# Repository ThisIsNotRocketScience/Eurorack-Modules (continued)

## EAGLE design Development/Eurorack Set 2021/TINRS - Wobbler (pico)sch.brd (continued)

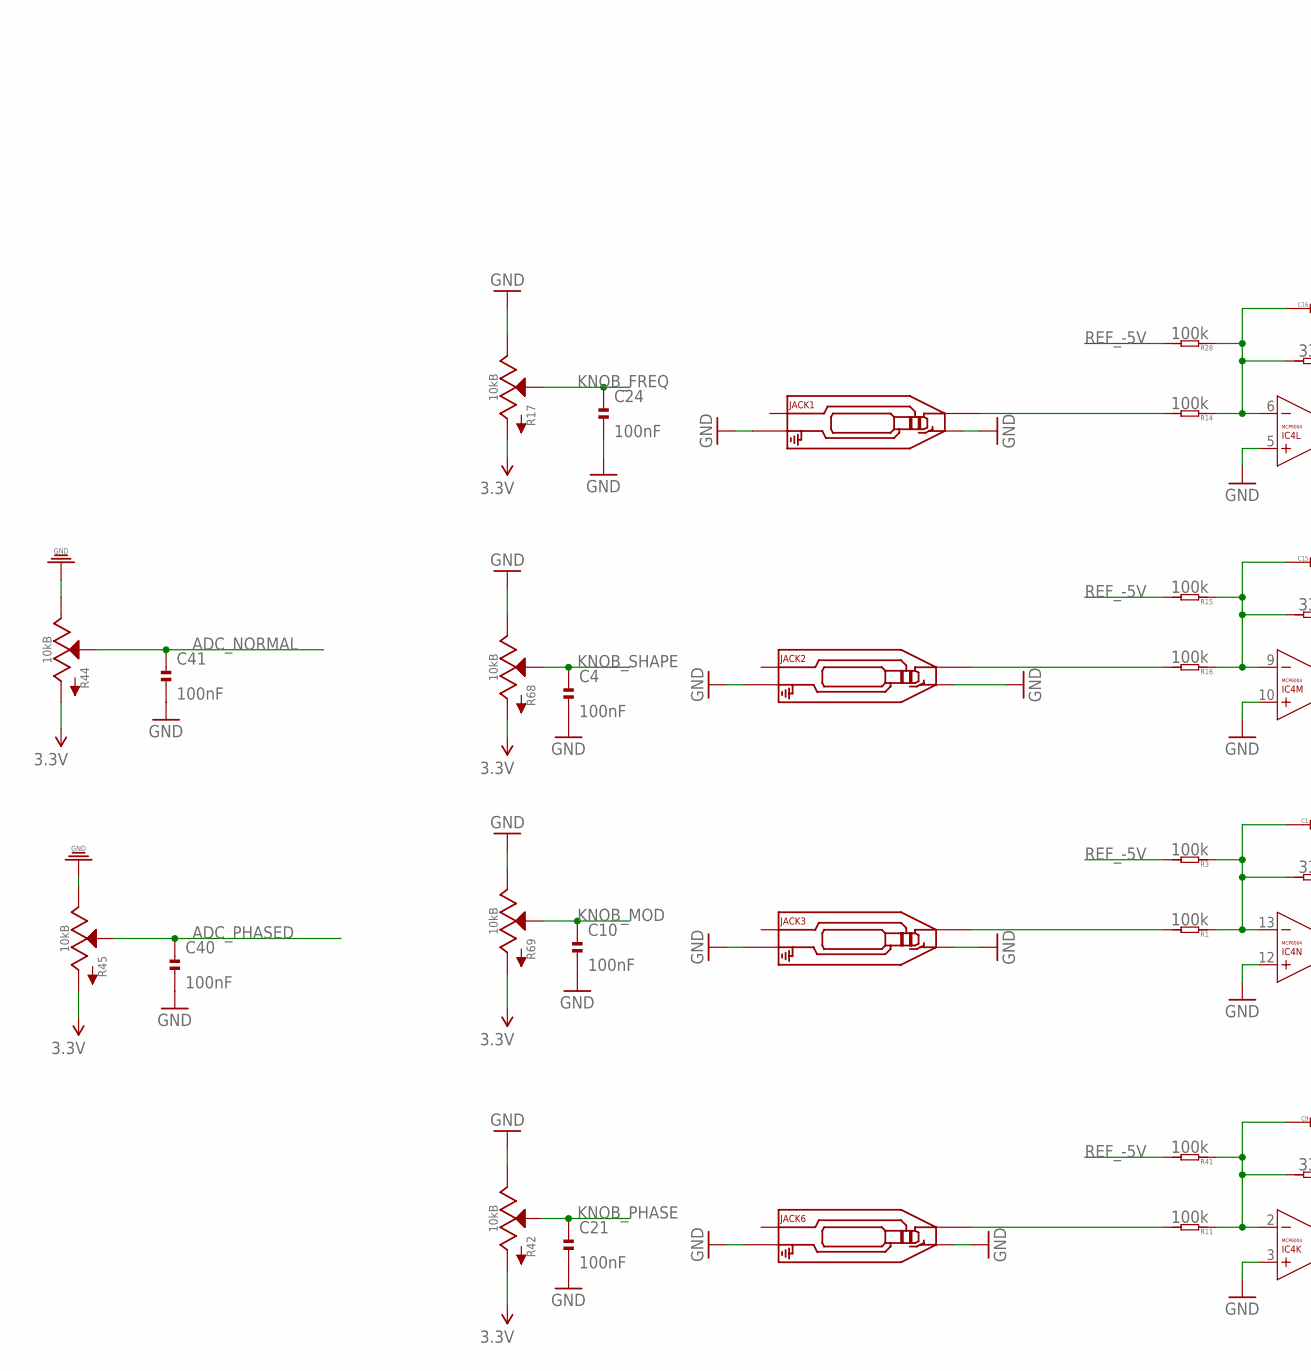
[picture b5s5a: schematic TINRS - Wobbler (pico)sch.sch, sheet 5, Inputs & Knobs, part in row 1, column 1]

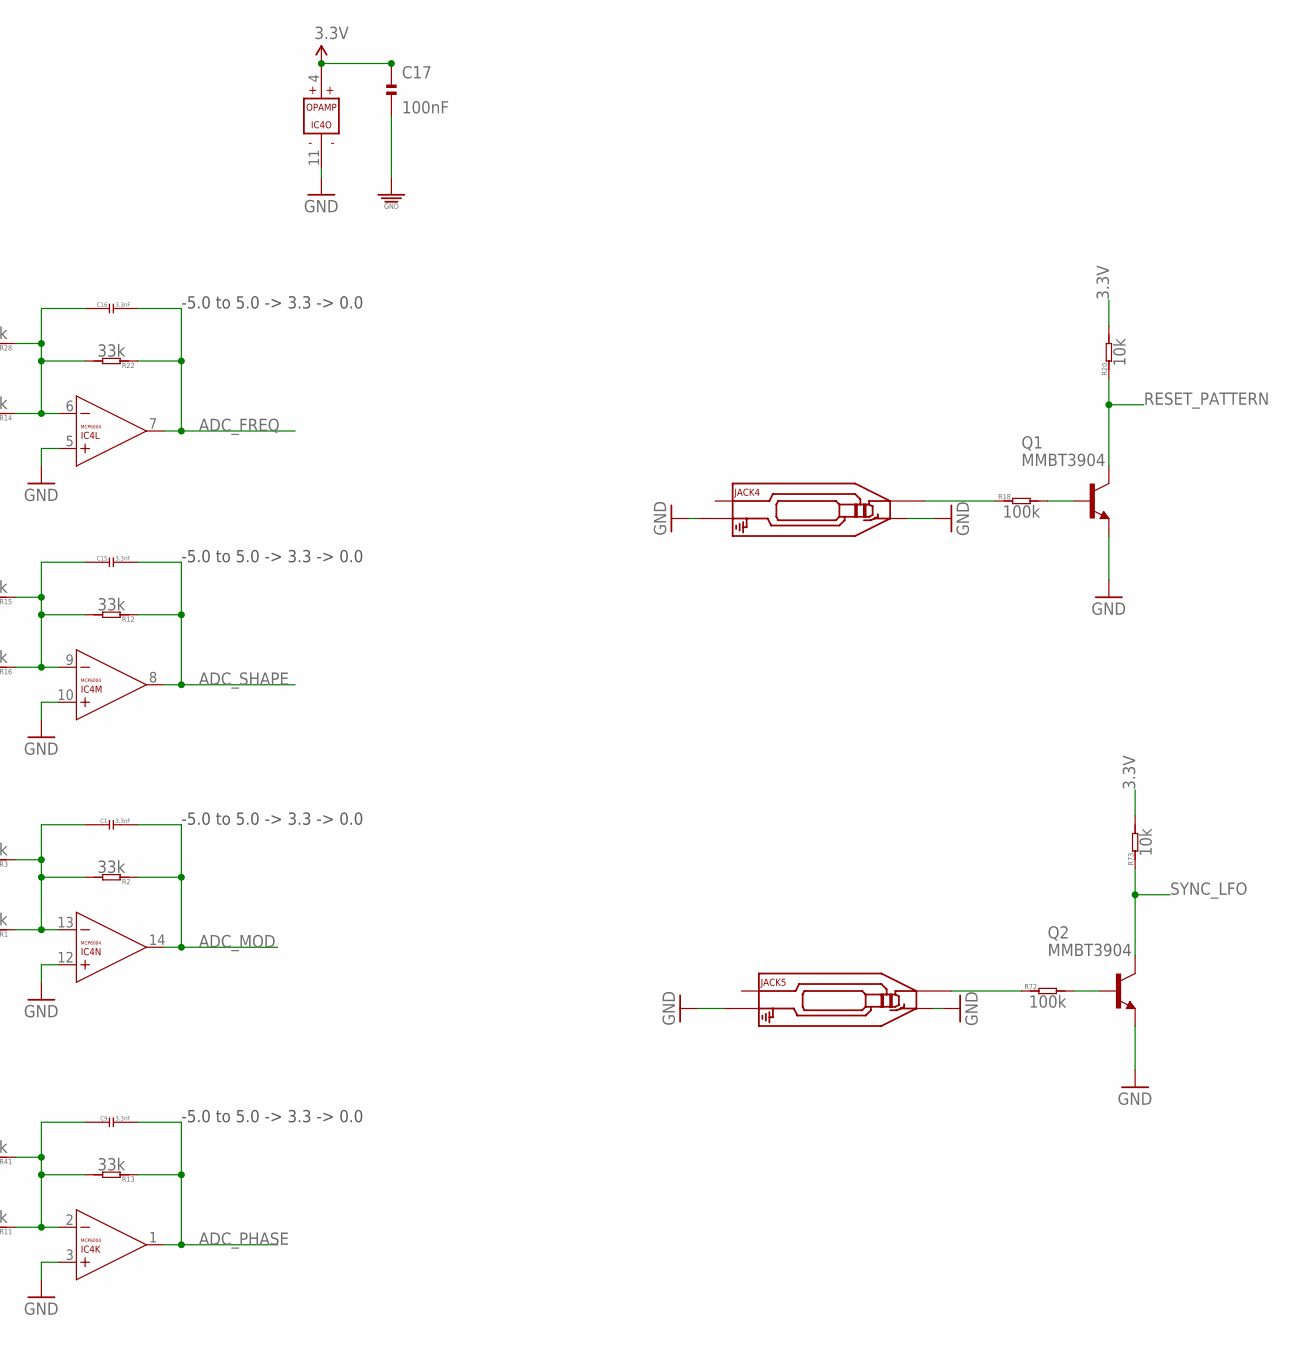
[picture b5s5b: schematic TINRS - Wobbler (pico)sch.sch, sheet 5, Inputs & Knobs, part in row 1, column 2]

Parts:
C1, C9, C15, C16: 3.3nF; C0603
C4, C10, C17, C21, C24, C40, C41: 100nF; C0402; MPN MC0603F104Z160CT
IC4: MCP6004; SO14; MPN MCP6004-I/SL.
JACK1, JACK2, JACK3, JACK4, JACK5, JACK6: AUDIO-JACK_SMALLSYMBOL; 3.5MM-JACK-SWITCH-13MM-NOHOLES-TESTPAD
Q1, Q2: MMBT3904; SOT23-BEC; MPN PMBT3904,215
R1, R3, R11, R14, R15, R16, R18, R28, R41, R72: 100k; R0603
R2, R12, R13, R22: 33k; R0603
R17, R42, R44, R45, R68, R69: 10kB; ALPS_POT_SQUAREHOLES
R20, R73: 10k; R0603

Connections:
3.3V: C17.1, IC4.4 (V+), R17.P$3 (A), R20.2, R42.P$3 (A), R44.P$3 (A), R45.P$3 (A), R68.P$3 (A), R69.P$3 (A), R73.2; also elsewhere on the board
ADC_FREQ: C16.2, IC4.7 (OUT), R22.1; also elsewhere on the board
ADC_MOD: C1.2, IC4.14 (OUT), R2.1; also elsewhere on the board
ADC_NORMAL: C41.1, R44.P$2 (S); also elsewhere on the board
ADC_PHASE: C9.2, IC4.1 (OUT), R13.1; also elsewhere on the board
ADC_PHASED: C40.1, R45.P$2 (S); also elsewhere on the board
ADC_SHAPE: C15.2, IC4.8 (OUT), R12.1; also elsewhere on the board
GND: C4.2, C10.2, C17.2, C21.2, C24.2, C40.2, C41.2, IC4.3 (+IN), IC4.5 (+IN), IC4.10 (+IN), IC4.11 (V-), IC4.12 (+IN), JACK1.RING_B@1 (RING), JACK1.RING_T@3 (RING), JACK1.SWITCH_B@1 (SWITCH), JACK1.SWITCH_T@3 (SWITCH), JACK2.RING_B@1 (RING), JACK2.RING_T@3 (RING), JACK2.SWITCH_B@1 (SWITCH), JACK2.SWITCH_T@3 (SWITCH), JACK3.RING_B@1 (RING), JACK3.RING_T@3 (RING), JACK3.SWITCH_B@1 (SWITCH), JACK3.SWITCH_T@3 (SWITCH), JACK4.RING_B@1 (RING), JACK4.RING_T@3 (RING), JACK4.SWITCH_B@1 (SWITCH), JACK4.SWITCH_T@3 (SWITCH), JACK5.RING_B@1 (RING), JACK5.RING_T@3 (RING), JACK5.SWITCH_B@1 (SWITCH), JACK5.SWITCH_T@3 (SWITCH), JACK6.RING_B@1 (RING), JACK6.RING_T@3 (RING), JACK6.SWITCH_B@1 (SWITCH), JACK6.SWITCH_T@3 (SWITCH), Q1.E, Q2.E, R17.P$1 (E), R42.P$1 (E), R44.P$1 (E), R45.P$1 (E), R68.P$1 (E), R69.P$1 (E); also elsewhere on the board
KNOB_FREQ: C24.1, R17.P$2 (S); also elsewhere on the board
KNOB_MOD: C10.1, R69.P$2 (S); also elsewhere on the board
KNOB_PHASE: C21.1, R42.P$2 (S); also elsewhere on the board
KNOB_SHAPE: C4.1, R68.P$2 (S); also elsewhere on the board
unnamed: JACK2.TIP_B@1 (TIP), JACK2.TIP_T@3 (TIP), R16.2
unnamed: C15.1, IC4.9 (-IN), R12.2, R15.1, R16.1
unnamed: JACK3.TIP_B@1 (TIP), JACK3.TIP_T@3 (TIP), R1.2
unnamed: C1.1, IC4.13 (-IN), R1.1, R2.2, R3.1
unnamed: JACK6.TIP_B@1 (TIP), JACK6.TIP_T@3 (TIP), R11.2
unnamed: C9.1, IC4.2 (-IN), R11.1, R13.2, R41.1
unnamed: Q1.B, R18.2
unnamed: JACK4.TIP_B@1 (TIP), JACK4.TIP_T@3 (TIP), R18.1
unnamed: JACK1.TIP_B@1 (TIP), JACK1.TIP_T@3 (TIP), R14.2
unnamed: C16.1, IC4.6 (-IN), R14.1, R22.2, R28.1
unnamed: Q2.B, R72.2
unnamed: JACK5.TIP_B@1 (TIP), JACK5.TIP_T@3 (TIP), R72.1
REF_-5V: R3.2, R15.2, R28.2, R41.2; also elsewhere on the board
RESET_PATTERN: Q1.C, R20.1; also elsewhere on the board
SYNC_LFO: Q2.C, R73.1; also elsewhere on the board

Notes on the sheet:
-5.0 to 5.0 -> 3.3 -> 0.0

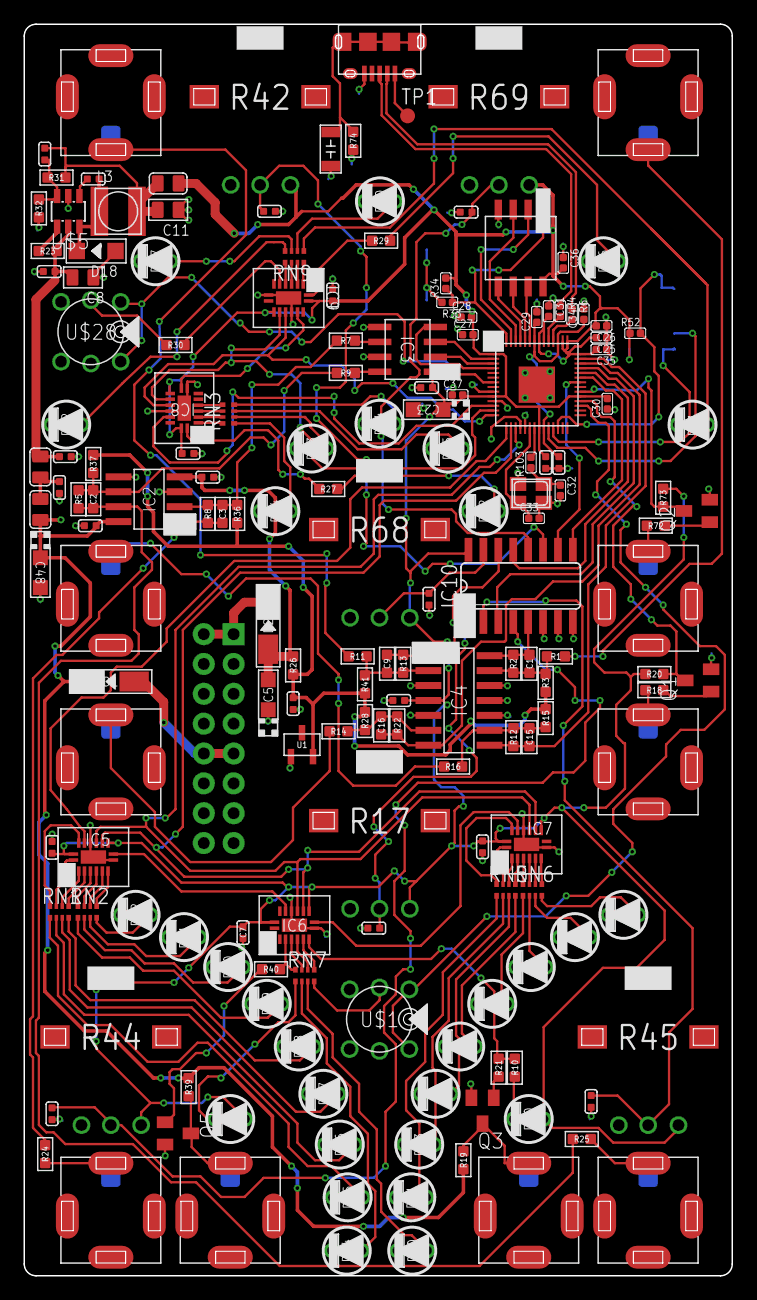
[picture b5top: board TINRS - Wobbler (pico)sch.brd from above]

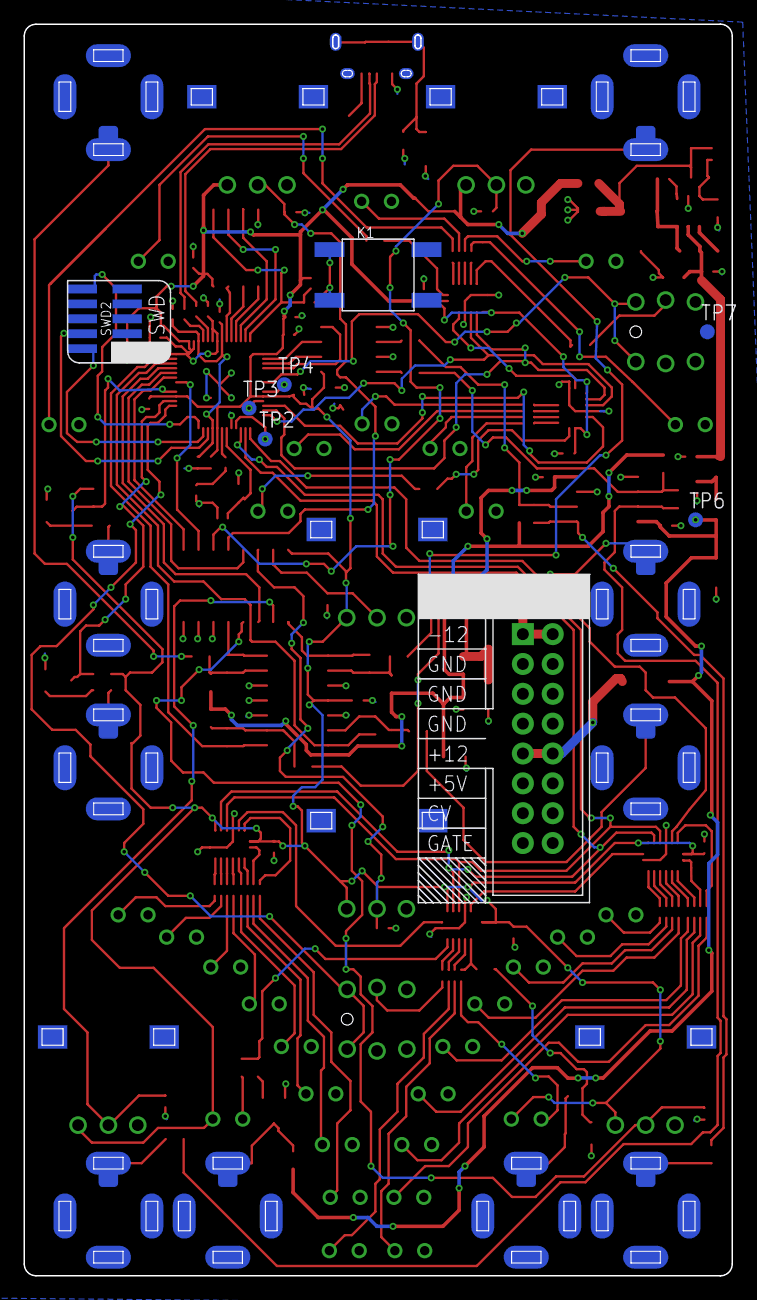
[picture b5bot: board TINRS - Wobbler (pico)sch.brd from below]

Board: 2 copper layers, 60.2 x 106.5 mm, 182 parts (8 on the bottom side), 155 nets.

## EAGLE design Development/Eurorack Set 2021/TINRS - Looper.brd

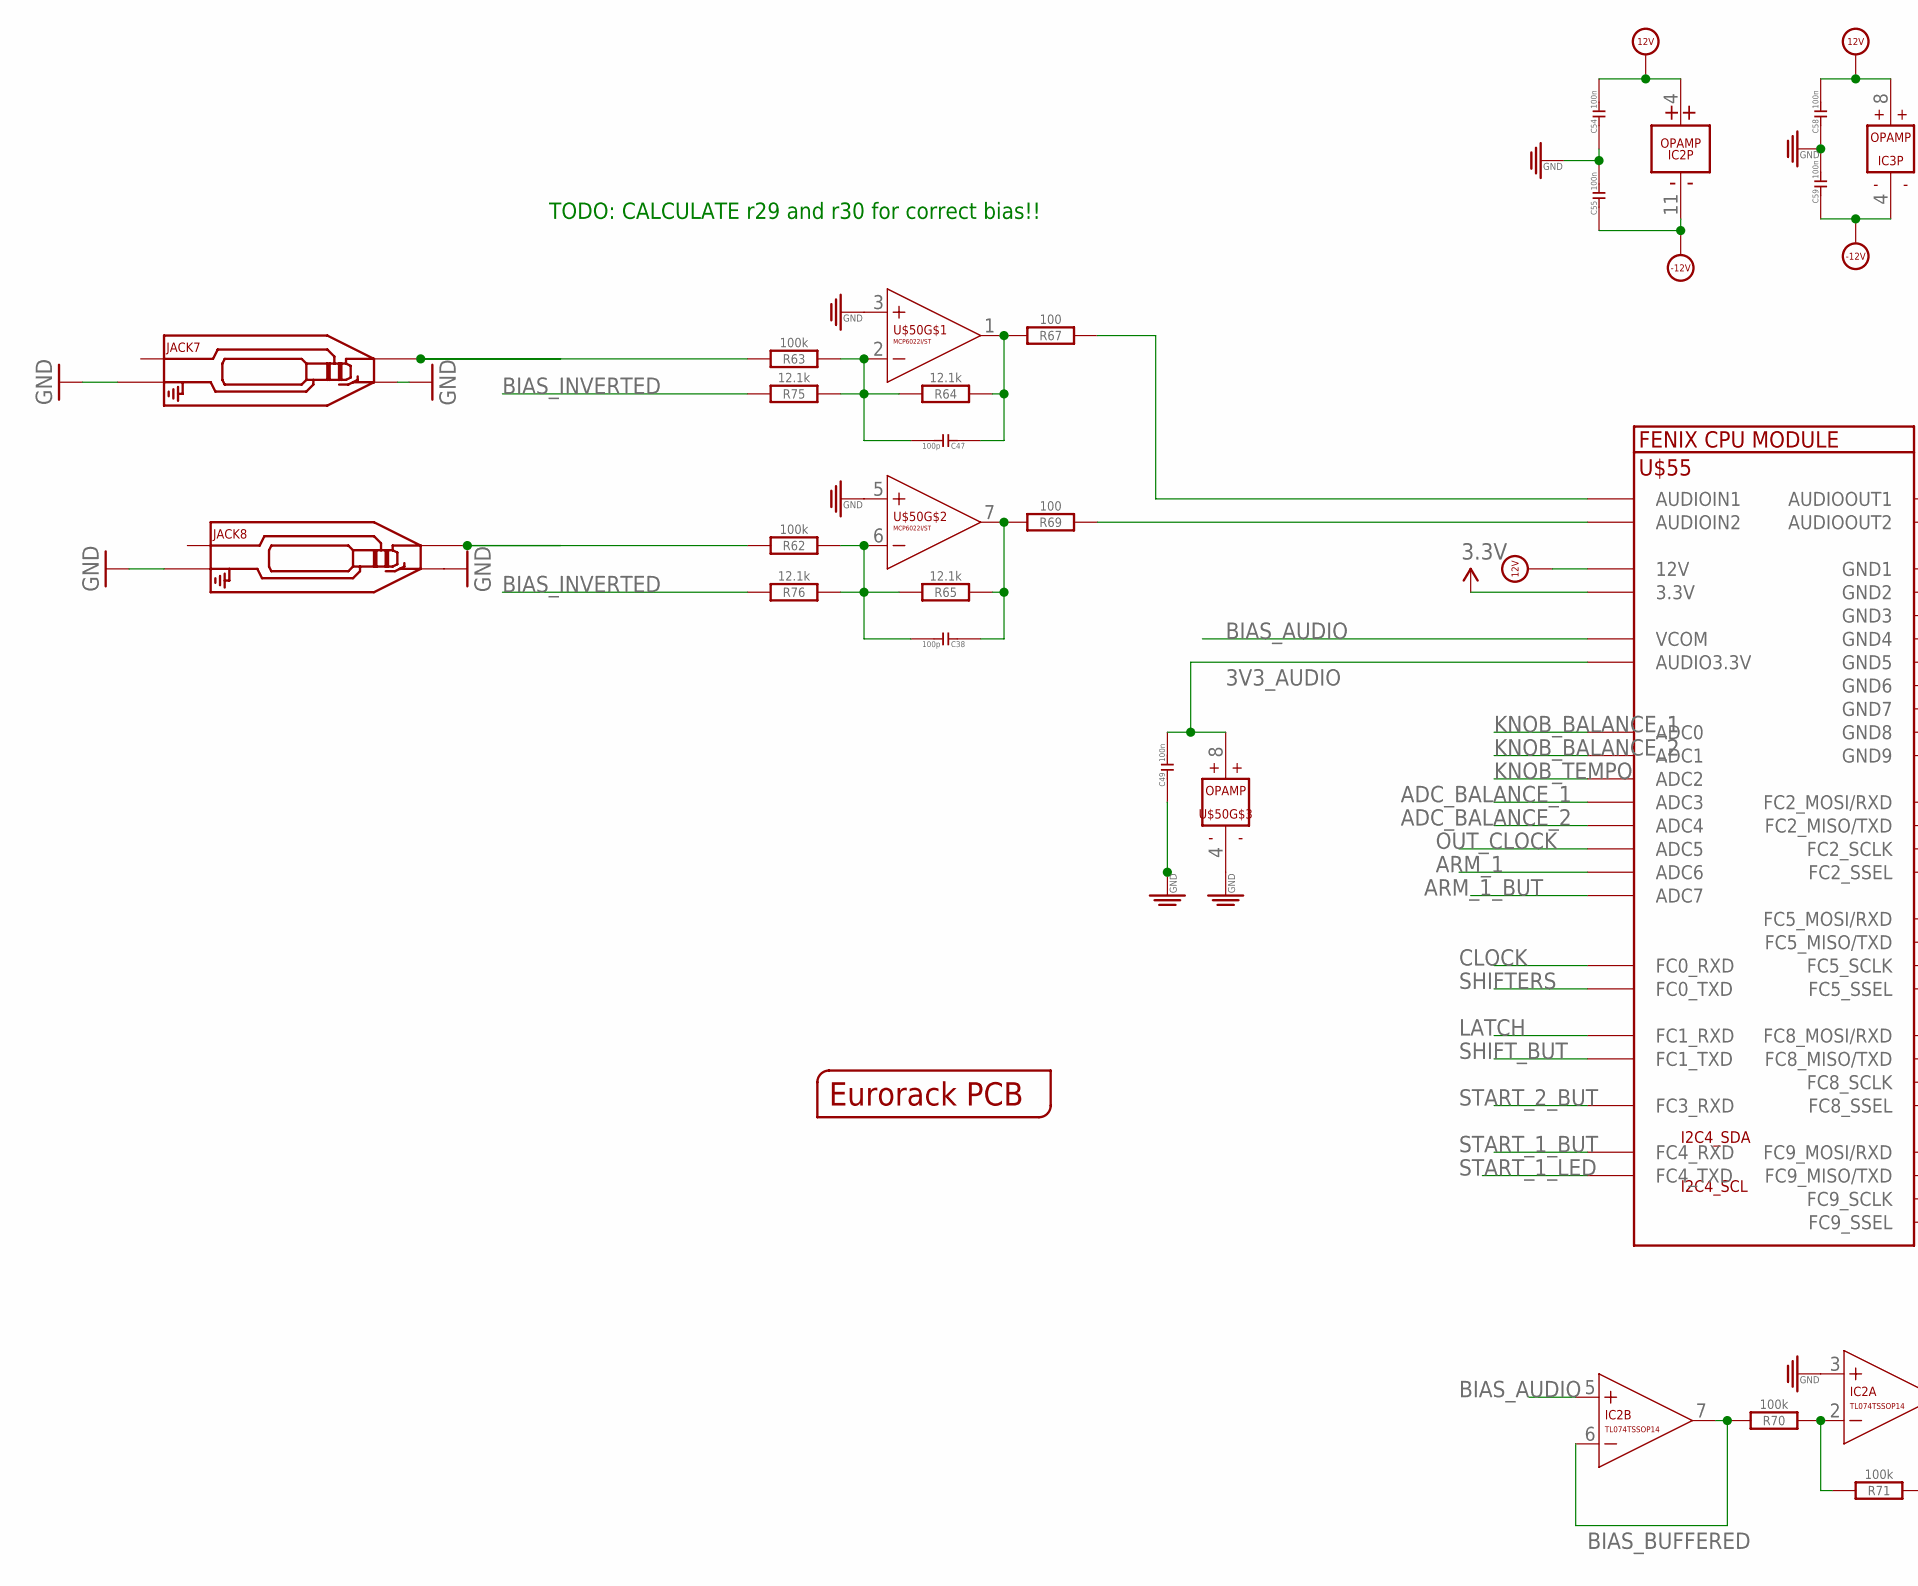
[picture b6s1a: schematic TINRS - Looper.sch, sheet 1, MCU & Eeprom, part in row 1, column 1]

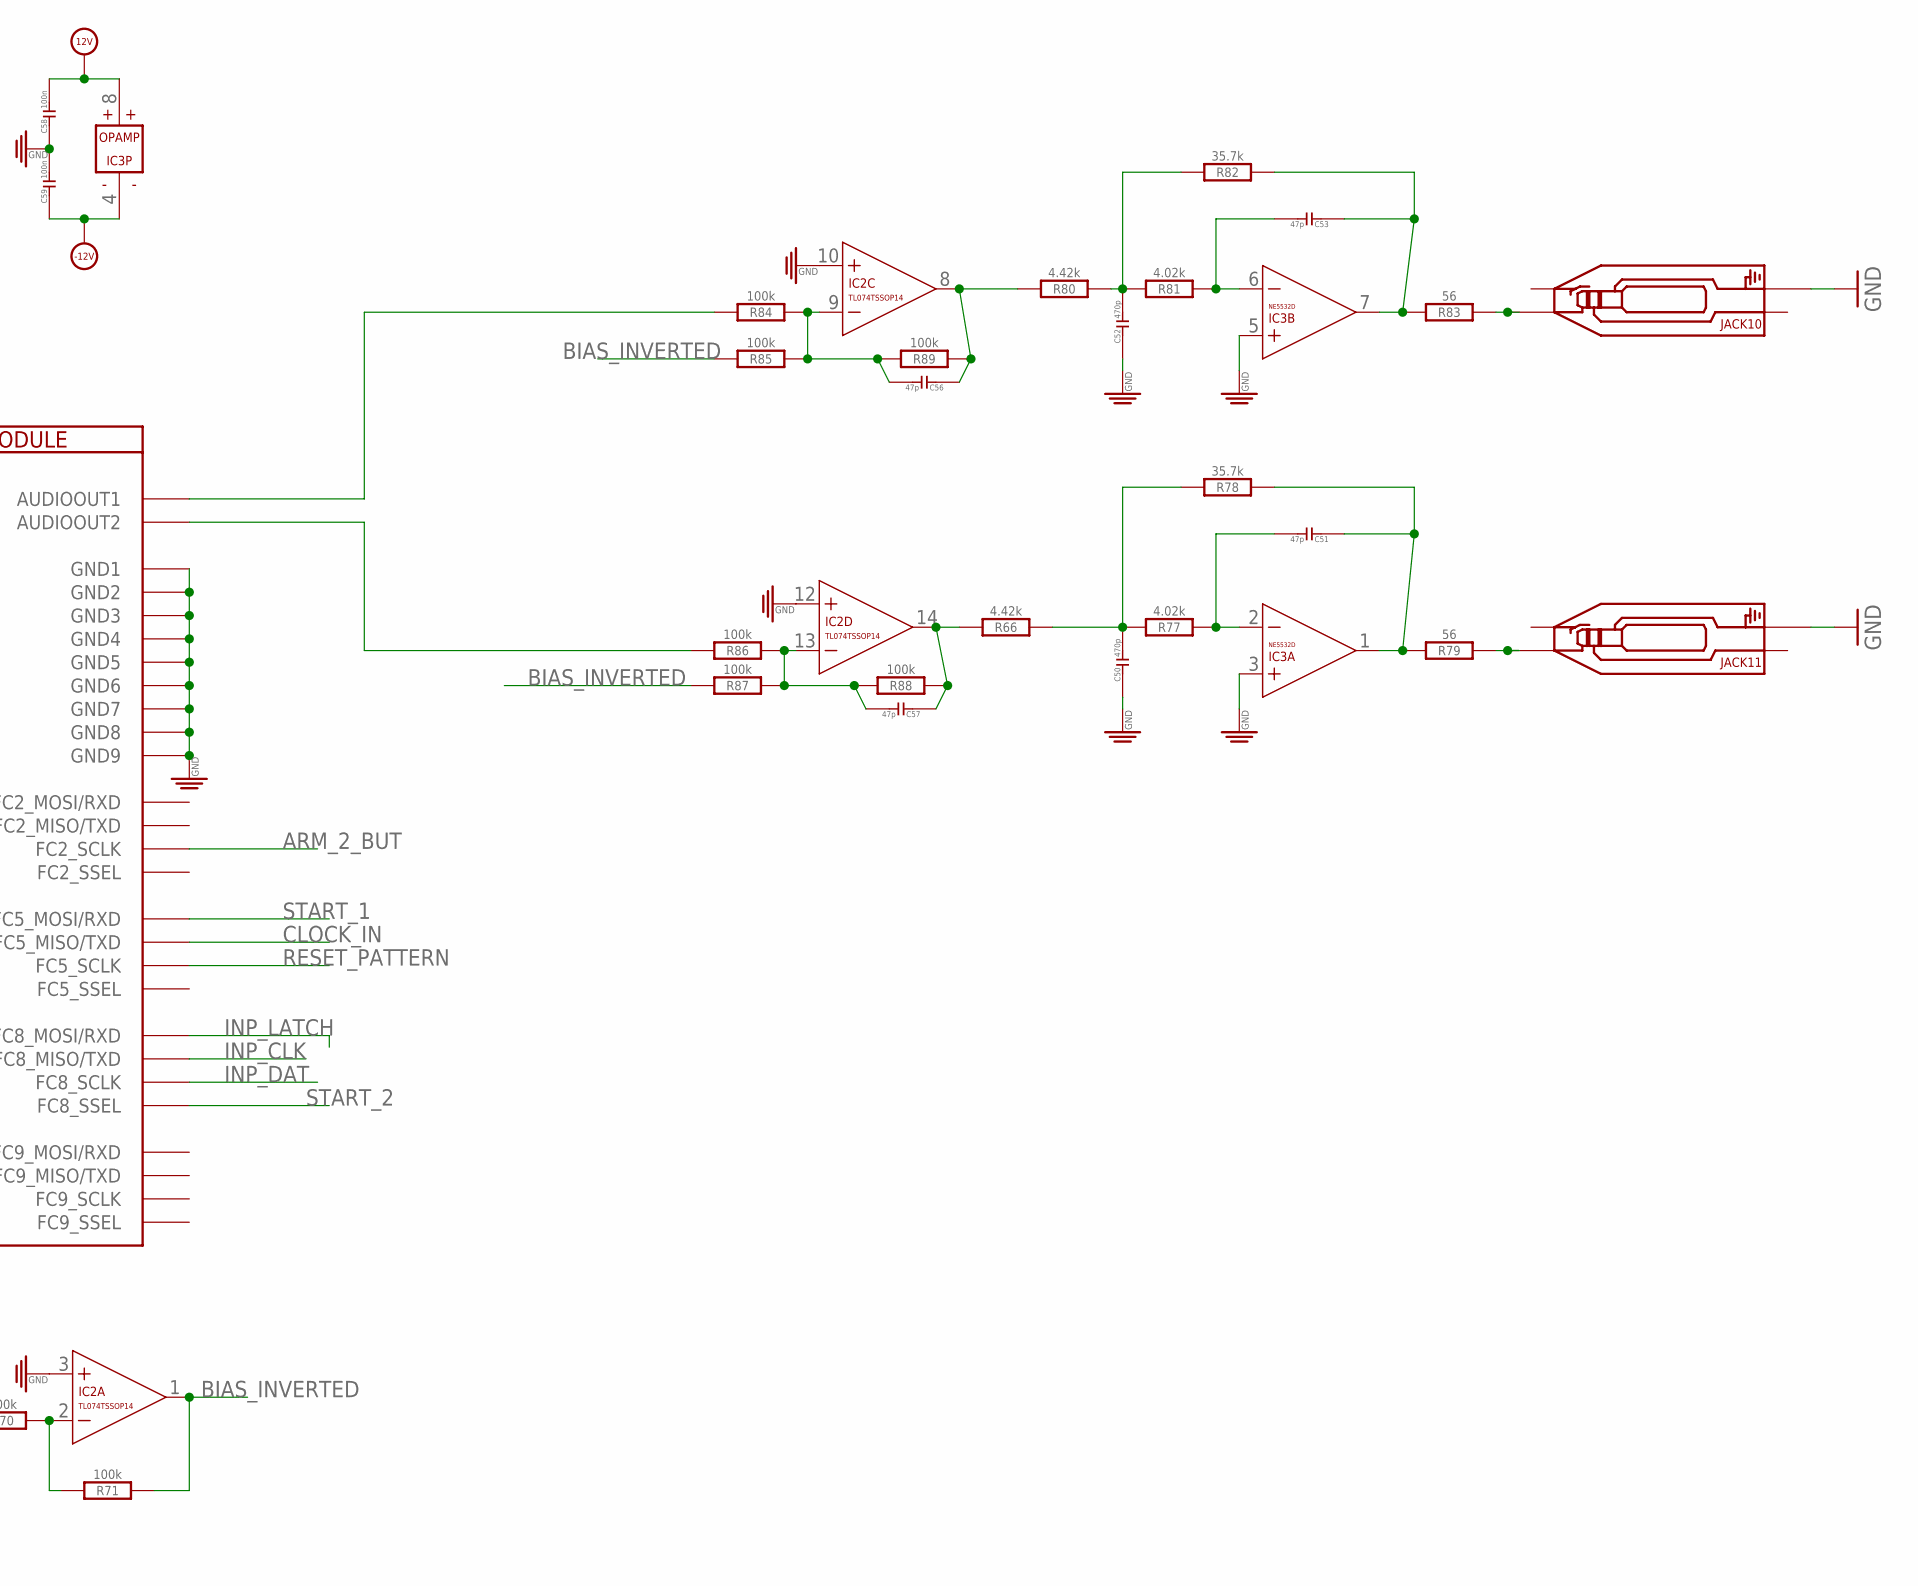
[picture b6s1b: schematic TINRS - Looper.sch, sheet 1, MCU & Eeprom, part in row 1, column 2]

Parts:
C38, C47: 100p; C0603
C49, C54, C55, C58, C59: 100n; C0603
C50, C52: 470p; C0603
C51, C53, C56, C57: 47p; C0603
IC2: TL074TSSOP14; TSSOP14
IC3: NE5532D; SO08
JACK7, JACK8, JACK10, JACK11: AUDIO-JACK_SMALLSYMBOL; 3.5MM-JACK-SWITCH-13MM-NOHOLES-TESTPAD
OUTLINE: EURORACK_PCB12HP; EURORACK12HPPCB
R62, R63, R70, R71, R84, R85, R86, R87, R88, R89: 100k; R0402
R64, R65, R75, R76: 12.1k; R0402
R66, R80: 4.42k; R0402
R67, R69: 100; R0402
R77, R81: 4.02k; R0402
R78, R82: 35.7k; R0402
R79, R83: 56; R0402
U$50: MCP6022I/ST; TSSOP8
U$55: MCUPLUGIN2; MCUPLUGIN

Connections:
3.3V: U$55.P$7 (3.3V); also elsewhere on the board
3V3_AUDIO: C49.2, U$50.8 (V+), U$55.P$48 (AUDIO3.3V)
12V: C54.2, C58.2, IC2.4 (V+), IC3.8 (V+), U$55.P$45 (12V); also elsewhere on the board
-12V: C55.1, C59.1, IC2.11 (V-), IC3.4 (V-); also elsewhere on the board
ADC_BALANCE_1: U$55.P$28 (ADC3); also elsewhere on the board
ADC_BALANCE_2: U$55.P$29 (ADC4); also elsewhere on the board
ARM_1: U$55.P$31 (ADC6); also elsewhere on the board
ARM_1_BUT: U$55.P$32 (ADC7); also elsewhere on the board
ARM_2_BUT: U$55.P$11 (FC2_SCLK); also elsewhere on the board
BIAS_AUDIO: IC2.5 (+IN), U$55.P$47 (VCOM)
BIAS_BUFFERED: IC2.6 (-IN), IC2.7 (OUT), R70.1
BIAS_INVERTED: IC2.1 (OUT), R71.2, R75.1, R76.1, R85.1, R87.1
CLOCK: U$55.P$36 (FC0_RXD); also elsewhere on the board
CLOCK_IN: U$55.P$21 (FC5_MISO/TXD); also elsewhere on the board
GND: C49.1, C50.1, C52.1, C54.1, C55.2, C58.1, C59.2, IC2.3 (+IN), IC2.10 (+IN), IC2.12 (+IN), IC3.3 (+IN), IC3.5 (+IN), JACK7.RING_B@1 (RING), JACK7.RING_T@3 (RING), JACK7.SWITCH_B@1 (SWITCH), JACK7.SWITCH_T@3 (SWITCH), JACK8.RING_B@1 (RING), JACK8.RING_T@3 (RING), JACK8.SWITCH_B@1 (SWITCH), JACK8.SWITCH_T@3 (SWITCH), JACK10.RING_B@1 (RING), JACK10.RING_T@3 (RING), JACK11.RING_B@1 (RING), JACK11.RING_T@3 (RING), U$50.3 (+IN), U$50.4 (V-), U$50.5 (+IN), U$55.P$1 (GND1), U$55.P$6 (GND2), U$55.P$8 (GND3), U$55.P$23 (GND4), U$55.P$24 (GND5), U$55.P$33 (GND6), U$55.P$39 (GND7), U$55.P$40 (GND8), U$55.P$46 (GND9); also elsewhere on the board
INP_CLK: U$55.P$13 (FC8_MISO/TXD); also elsewhere on the board
INP_DAT: U$55.P$15 (FC8_SCLK); also elsewhere on the board
INP_LATCH: U$55.P$14 (FC8_MOSI/RXD); also elsewhere on the board
KNOB_BALANCE_1: U$55.P$25 (ADC0); also elsewhere on the board
KNOB_BALANCE_2: U$55.P$26 (ADC1); also elsewhere on the board
KNOB_TEMPO: U$55.P$27 (ADC2); also elsewhere on the board
LATCH: U$55.P$38 (FC1_RXD); also elsewhere on the board
unnamed: C38.2, R62.2, R65.1, R76.2, U$50.6 (-IN)
unnamed: C47.2, R63.2, R64.1, R75.2, U$50.2 (-IN)
unnamed: C38.1, R65.2, R69.1, U$50.7 (OUT)
unnamed: C47.1, R64.2, R67.1, U$50.1 (OUT)
unnamed: IC2.2 (-IN), R70.2, R71.1
unnamed: C51.2, IC3.2 (-IN), R77.2
unnamed: C50.2, R66.2, R77.1, R78.1
unnamed: C51.1, IC3.1 (OUT), R78.2, R79.1
unnamed: JACK11.TIP_B@1 (TIP), JACK11.TIP_T@3 (TIP), R79.2
unnamed: C53.2, IC3.6 (-IN), R81.2
unnamed: C52.2, R80.2, R81.1, R82.1
unnamed: C53.1, IC3.7 (OUT), R82.2, R83.1
unnamed: JACK10.TIP_B@1 (TIP), JACK10.TIP_T@3 (TIP), R83.2
unnamed: C56.2, IC2.9 (-IN), R84.2, R85.2, R89.1
unnamed: C57.2, IC2.13 (-IN), R86.2, R87.2, R88.1
unnamed: C56.1, IC2.8 (OUT), R80.1, R89.2
unnamed: R86.1, U$55.P$44 (AUDIOOUT2)
unnamed: R84.1, U$55.P$42 (AUDIOOUT1)
unnamed: C57.1, IC2.14 (OUT), R66.1, R88.2
unnamed: JACK7.TIP_B@1 (TIP), JACK7.TIP_T@3 (TIP), R63.1
unnamed: JACK8.TIP_B@1 (TIP), JACK8.TIP_T@3 (TIP), R62.1
OUT_CLOCK: U$55.P$30 (ADC5); also elsewhere on the board
RESET_PATTERN: U$55.P$20 (FC5_SCLK); also elsewhere on the board
SHIFTERS: U$55.P$35 (FC0_TXD); also elsewhere on the board
SHIFT_BUT: U$55.P$37 (FC1_TXD); also elsewhere on the board
START_1: U$55.P$22 (FC5_MOSI/RXD); also elsewhere on the board
START_1_BUT: U$55.P$18 (FC4_RXD); also elsewhere on the board
START_1_LED: U$55.P$17 (FC4_TXD); also elsewhere on the board
START_2: U$55.P$16 (FC8_SSEL); also elsewhere on the board
START_2_BUT: U$55.P$34 (FC3_RXD); also elsewhere on the board
TO_AUDIOIN_1: R67.2, U$55.P$41 (AUDIOIN1)
TO_AUDIOIN_2: R69.2, U$55.P$43 (AUDIOIN2)

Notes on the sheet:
TODO: CALCULATE r29 and r30 for correct bias!!

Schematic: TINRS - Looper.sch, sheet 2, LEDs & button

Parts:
C1, C2, C7, C14, C20: 100nF; C0402; MPN MC0603F104Z160CT
D3, D6, D7, D8, D9: yellow; 3MMLED
IC1, IC8: 74HC165D; SO16
IC5, IC6, IC7: 74HC595BQ; QFN50P250X350X100-17N
JACK9: AUDIO-JACK_SMALLSYMBOL; 3.5MM-JACK-SWITCH-13MM-NOHOLES-TESTPAD
Q5: MMBT3904; SOT23-BEC; MPN PMBT3904,215
R5, R7, R8, R9, R10, R21, R24, R29, R30, R33, R34, R35, R38, R41, R45, R46, R49, R50, R52, R54, R55, R58, R59, R74, R90, R95: 56; R0402
R13, R19, R25, R27, R36, R37, R39, R42, R43, R47, R48, R51, R53, R56, R57, R60, R61, R91, R92, R93, R94, R96: 10k; R0402
R40: 100k; R0402
U$1, U$11, U$12, U$13, U$23, U$24, U$28, U$31, U$32, U$33, U$34, U$35, U$36, U$37, U$38, U$39, U$40, U$41, U$42, U$43, U$44: SWITCH_W_LED_PB6149L-X-102YELLOW; PB6149L

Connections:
1_1_BUT: IC1.14 (D), R13.2, U$23.1, U$23.2
1_1_LED: IC5.4 (Q4), R9.2
1_2_BUT: IC1.13 (C), R25.2, U$31.1, U$31.2
1_2_LED: IC5.6 (Q6), R21.2
1_3_BUT: IC1.12 (B), R36.2, U$33.1, U$33.2
1_3_LED: IC5.5 (Q5), R29.2
1_4_BUT: IC1.11 (A), R42.2, U$35.1, U$35.2
1_4_LED: IC5.7 (Q7), R38.2
1_5_BUT: IC1.3 (E), R47.2, U$37.1, U$37.2
1_5_LED: IC5.15 (Q0), R45.2
1_6_BUT: IC1.4 (F), R51.2, U$39.1, U$39.2
1_6_LED: IC5.1 (Q1), R49.2
1_7_BUT: IC1.5 (G), R56.2, U$41.1, U$41.2
1_7_LED: IC5.2 (Q2), R54.2
1_8_BUT: IC1.6 (H), R60.2, U$43.1, U$43.2
1_8_LED: IC5.3 (Q3), R58.2
2_1_BUT: IC8.11 (A), R19.2, U$24.1, U$24.2
2_1_LED: IC7.15 (Q0), R10.2
2_2_BUT: IC8.12 (B), R27.2, U$32.1, U$32.2
2_2_LED: IC7.1 (Q1), R24.2
2_3_BUT: IC8.13 (C), R37.2, U$34.1, U$34.2
2_3_LED: IC7.2 (Q2), R35.2
2_4_BUT: IC8.14 (D), R43.2, U$36.1, U$36.2
2_4_LED: IC7.3 (Q3), R41.2
2_5_BUT: IC8.3 (E), R48.2, U$38.1, U$38.2
2_5_LED: IC7.4 (Q4), R46.2
2_6_BUT: IC8.4 (F), R53.2, U$40.1, U$40.2
2_6_LED: IC7.5 (Q5), R50.2
2_7_BUT: IC8.5 (G), R57.2, U$42.1, U$42.2
2_7_LED: IC7.6 (Q6), R55.2
2_8_BUT: IC8.6 (H), R61.2, U$44.1, U$44.2
2_8_LED: IC7.7 (Q7), R59.2
3.3V: C1.2, C2.2, C7.2, C14.2, C20.2, D3.+, IC1.16 (VCC), IC5.10 (!MR), IC5.16 (VCC), IC6.10 (!MR), IC6.16 (VCC), IC7.10 (!MR), IC7.16 (VCC), IC8.16 (VCC), R13.1, R19.1, R25.1, R27.1, R36.1, R37.1, R42.1, R43.1, R47.1, R48.1, R51.1, R53.1, R56.1, R57.1, R60.1, R61.1, R91.1, R92.1, R93.1, R94.1, R96.1; also elsewhere on the board
12V: R39.2; also elsewhere on the board
ARM_1_BUT: R92.2, U$28.1, U$28.2; also elsewhere on the board
ARM_1_LED: IC6.4 (Q4), R30.2
ARM_2_BUT: R91.2, U$13.1, U$13.2; also elsewhere on the board
ARM_2_LED: IC6.5 (Q5), R8.2
CLOCK: IC5.11 (SHCP), IC6.11 (SHCP), IC7.11 (SHCP); also elsewhere on the board
GND: C1.1, C2.1, C7.1, C14.1, C20.1, D6.-, D7.-, D8.-, D9.-, IC1.8 (GND), IC1.10 (SER), IC1.15 (INH), IC5.8 (GND), IC5.13 (!OE), IC5.17 (GND_2), IC6.8 (GND), IC6.13 (!OE), IC6.17 (GND_2), IC7.8 (GND), IC7.13 (!OE), IC7.17 (GND_2), IC8.8 (GND), IC8.15 (INH), JACK9.RING_B@1 (RING), JACK9.RING_T@3 (RING), Q5.E, U$1.3, U$1.4, U$1.LEDNEG (NEG), U$11.3, U$11.4, U$11.LEDNEG (NEG), U$12.3, U$12.4, U$12.LEDNEG (NEG), U$13.3, U$13.4, U$13.LEDNEG (NEG), U$23.3, U$23.4, U$23.LEDNEG (NEG), U$24.3, U$24.4, U$24.LEDNEG (NEG), U$28.3, U$28.4, U$28.LEDNEG (NEG), U$31.3, U$31.4, U$31.LEDNEG (NEG), U$32.3, U$32.4, U$32.LEDNEG (NEG), U$33.3, U$33.4, U$33.LEDNEG (NEG), U$34.3, U$34.4, U$34.LEDNEG (NEG), U$35.3, U$35.4, U$35.LEDNEG (NEG), U$36.3, U$36.4, U$36.LEDNEG (NEG), U$37.3, U$37.4, U$37.LEDNEG (NEG), U$38.3, U$38.4, U$38.LEDNEG (NEG), U$39.3, U$39.4, U$39.LEDNEG (NEG), U$40.3, U$40.4, U$40.LEDNEG (NEG), U$41.3, U$41.4, U$41.LEDNEG (NEG), U$42.3, U$42.4, U$42.LEDNEG (NEG), U$43.3, U$43.4, U$43.LEDNEG (NEG), U$44.3, U$44.4, U$44.LEDNEG (NEG); also elsewhere on the board
INP_CLK: IC1.2 (CLK), IC8.2 (CLK); also elsewhere on the board
INP_DAT: IC8.9 (QH); also elsewhere on the board
INP_LATCH: IC1.1 (SH/!LD), IC8.1 (SH/!LD); also elsewhere on the board
LATCH: IC5.12 (STCP), IC6.12 (STCP), IC7.12 (STCP); also elsewhere on the board
unnamed: R5.1, U$11.LEDPOS (POS)
unnamed: R7.1, U$12.LEDPOS (POS)
unnamed: R8.1, U$13.LEDPOS (POS)
unnamed: R9.1, U$23.LEDPOS (POS)
unnamed: D7.+, R52.1
unnamed: IC1.9 (QH), IC8.10 (SER)
unnamed: R10.1, U$24.LEDPOS (POS)
unnamed: R21.1, U$31.LEDPOS (POS)
unnamed: R24.1, U$32.LEDPOS (POS)
unnamed: IC6.7 (Q7), R33.2
unnamed: R29.1, U$33.LEDPOS (POS)
unnamed: D3.-, R95.2
unnamed: R35.1, U$34.LEDPOS (POS)
unnamed: R38.1, U$35.LEDPOS (POS)
unnamed: R41.1, U$36.LEDPOS (POS)
unnamed: R45.1, U$37.LEDPOS (POS)
unnamed: IC6.2 (Q2), R34.2
unnamed: IC6.1 (Q1), R52.2
unnamed: IC6.15 (Q0), R74.2
unnamed: R46.1, U$38.LEDPOS (POS)
unnamed: D6.+, R74.1
unnamed: D8.+, R34.1
unnamed: D9.+, R33.1
unnamed: R49.1, U$39.LEDPOS (POS)
unnamed: R50.1, U$40.LEDPOS (POS)
unnamed: R54.1, U$41.LEDPOS (POS)
unnamed: R55.1, U$42.LEDPOS (POS)
unnamed: Q5.B, R40.2
unnamed: JACK9.TIP_B@1 (TIP), JACK9.TIP_T@3 (TIP), Q5.C, R39.1
unnamed: R58.1, U$43.LEDPOS (POS)
unnamed: R59.1, U$44.LEDPOS (POS)
unnamed: R30.1, U$28.LEDPOS (POS)
OUT_CLOCK: R40.1, R95.1; also elsewhere on the board
SHIFTER1TO2: IC5.9 (Q7S), IC6.14 (DS)
SHIFTERS: IC5.14 (DS); also elsewhere on the board
SHIFTERS2TO3: IC6.9 (Q7S), IC7.14 (DS)
SHIFT_BUT: R96.2, U$1.1, U$1.2; also elsewhere on the board
SHIFT_LED: IC6.6 (Q6), R90.2
SHIFT_LED_L: R90.1, U$1.LEDPOS (POS)
START_1_BUT: R94.2, U$11.1, U$11.2; also elsewhere on the board
START_1_LED: R5.2; also elsewhere on the board
START_2_BUT: R93.2, U$12.1, U$12.2; also elsewhere on the board
START_2_LED: IC6.3 (Q3), R7.2

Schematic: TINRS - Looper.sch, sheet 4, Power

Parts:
C5, C23, C48: 10uF; CASE-A_3216; MPN TAJB106K020RNJ
C6: 100nF; C0402; MPN 06035C104KAT2A
C8: 10u; C0805
C11: 22u; C0805
C42: 10n; C0402; MPN MC0603F104Z160CT
C43, C44, C45: 100nF; C0402; MPN MC0603F104Z160CT
C46: 33p; C0402; MPN MC0603F104Z160CT
D1, D2: MRA4004T3G; DO-214AC; MPN US1G-E3/5AT
D18: schottky; SOD123
J14: POWER_SIMPLE10; POWER_10
L1, L2, L4: 0.1uH C76737; L0805
L3: 4.7uH; L0420
R23: 100k; R0402
R26: 10k; R0402
R31: 49.9k; R0402
R32: 16.2k; R0402
TP6, TP7: PTR1B1,27; B1,27
U1: LM4040DIM3-5.0; SOT95P237X112-3N
U$5: BL9342; SOT23-6

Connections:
3.3V: C23.+ (1), L4.2; also elsewhere on the board
12V: C48.+ (1), D1.2 (-), L1.1, TP6.TP; also elsewhere on the board
-12V: C5.- (2), D2.1 (+), R26.1; also elsewhere on the board
GND: C5.+ (1), C6.1, C8.1, C11.1, C23.- (2), C42.1, C43.1, C44.1, C48.- (2), D18.+, J14.3 (GND), J14.4 (GND), J14.5 (GND), J14.6 (GND), J14.7 (GND), J14.8 (GND), R32.2, TP7.TP, U1.1 (CATHODE), U$5.2 (GND); also elsewhere on the board
unnamed: D1.1 (+), J14.9 (+12V), J14.10 (+12V)
unnamed: D2.2 (-), J14.1 (-12V), J14.2 (-12V)
unnamed: C42.2, L1.2, L2.1
unnamed: C8.2, C43.2, C44.2, L2.2, R23.2, U$5.5 (VIN)
unnamed: C45.2, U$5.1 (BST)
unnamed: C45.1, D18.-, L3.1, U$5.6 (SW)
unnamed: C46.2, R31.2, R32.1, U$5.3 (FB)
unnamed: C11.2, C46.1, L3.2, L4.1, R31.1
unnamed: R23.1, U$5.4 (EN)
REF_-5V: C6.2, R26.2, U1.2 (ANODE); also elsewhere on the board

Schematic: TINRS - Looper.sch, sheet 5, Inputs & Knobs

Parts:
C4, C17, C24, C41: 100nF; C0402; MPN MC0603F104Z160CT
C15, C16: 3.3nF; C0603
IC4: MCP6004; SO14; MPN MCP6004-I/SL.
JACK1, JACK2, JACK3, JACK4, JACK5, JACK6, JACK12: AUDIO-JACK_SMALLSYMBOL; 3.5MM-JACK-SWITCH-13MM-NOHOLES-TESTPAD
Q1, Q2, Q3, Q6, Q7: MMBT3904; SOT23-BEC; MPN PMBT3904,215
R1, R3, R4, R14, R15, R16, R18, R28, R72: 100k; R0402
R2, R6, R11, R20, R73: 10k; R0402
R12, R22: 33k; R0402
R17, R44, R68: 10kB; ALPS_POT_SQUAREHOLES

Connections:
3.3V: C17.1, IC4.4 (V+), R2.2, R6.2, R11.2, R17.P$3 (A), R20.2, R44.P$3 (A), R68.P$3 (A), R73.2; also elsewhere on the board
ADC_BALANCE_1: C16.2, IC4.7 (OUT), R22.1; also elsewhere on the board
ADC_BALANCE_2: C15.2, IC4.8 (OUT), R12.1; also elsewhere on the board
ARM_1: Q3.C, R6.1; also elsewhere on the board
CLOCK_IN: Q2.C, R73.1; also elsewhere on the board
GND: C4.2, C17.2, C24.2, C41.2, IC4.3 (+IN), IC4.5 (+IN), IC4.10 (+IN), IC4.11 (V-), IC4.12 (+IN), JACK1.RING_B@1 (RING), JACK1.RING_T@3 (RING), JACK1.SWITCH_B@1 (SWITCH), JACK1.SWITCH_T@3 (SWITCH), JACK2.RING_B@1 (RING), JACK2.RING_T@3 (RING), JACK2.SWITCH_B@1 (SWITCH), JACK2.SWITCH_T@3 (SWITCH), JACK3.RING_B@1 (RING), JACK3.RING_T@3 (RING), JACK3.SWITCH_B@1 (SWITCH), JACK3.SWITCH_T@3 (SWITCH), JACK4.RING_B@1 (RING), JACK4.RING_T@3 (RING), JACK4.SWITCH_B@1 (SWITCH), JACK4.SWITCH_T@3 (SWITCH), JACK5.RING_B@1 (RING), JACK5.RING_T@3 (RING), JACK5.SWITCH_B@1 (SWITCH), JACK5.SWITCH_T@3 (SWITCH), JACK6.RING_B@1 (RING), JACK6.RING_T@3 (RING), JACK6.SWITCH_B@1 (SWITCH), JACK6.SWITCH_T@3 (SWITCH), JACK12.RING_B@1 (RING), JACK12.RING_T@3 (RING), JACK12.SWITCH_B@1 (SWITCH), JACK12.SWITCH_T@3 (SWITCH), Q1.E, Q2.E, Q3.E, Q6.E, Q7.E, R17.P$1 (E), R44.P$1 (E), R68.P$1 (E); also elsewhere on the board
KNOB_BALANCE_1: C24.1, R17.P$2 (S); also elsewhere on the board
KNOB_BALANCE_2: C4.1, R68.P$2 (S); also elsewhere on the board
KNOB_TEMPO: C41.1, R44.P$2 (S); also elsewhere on the board
unnamed: Q3.B, R4.2
unnamed: JACK2.TIP_B@1 (TIP), JACK2.TIP_T@3 (TIP), R16.2
unnamed: C15.1, IC4.9 (-IN), R12.2, R15.1, R16.1
unnamed: Q6.B, R1.2
unnamed: JACK3.TIP_B@1 (TIP), JACK3.TIP_T@3 (TIP), R1.1
unnamed: Q7.B, R3.2
unnamed: JACK6.TIP_B@1 (TIP), JACK6.TIP_T@3 (TIP), R3.1
unnamed: Q1.B, R18.2
unnamed: JACK4.TIP_B@1 (TIP), JACK4.TIP_T@3 (TIP), R18.1
unnamed: JACK12.TIP_B@1 (TIP), JACK12.TIP_T@3 (TIP), R4.1
unnamed: JACK1.TIP_B@1 (TIP), JACK1.TIP_T@3 (TIP), R14.2
unnamed: C16.1, IC4.6 (-IN), R14.1, R22.2, R28.1
unnamed: Q2.B, R72.2
unnamed: JACK5.TIP_B@1 (TIP), JACK5.TIP_T@3 (TIP), R72.1
unnamed: IC4.13 (-IN), IC4.14 (OUT)
unnamed: IC4.1 (OUT), IC4.2 (-IN)
REF_-5V: R15.2, R28.2; also elsewhere on the board
RESET_PATTERN: Q1.C, R20.1; also elsewhere on the board
START_1: Q6.C, R2.1; also elsewhere on the board
START_2: Q7.C, R11.1; also elsewhere on the board

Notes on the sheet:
-5.0 to 5.0 -> 3.3 -> 0.0
